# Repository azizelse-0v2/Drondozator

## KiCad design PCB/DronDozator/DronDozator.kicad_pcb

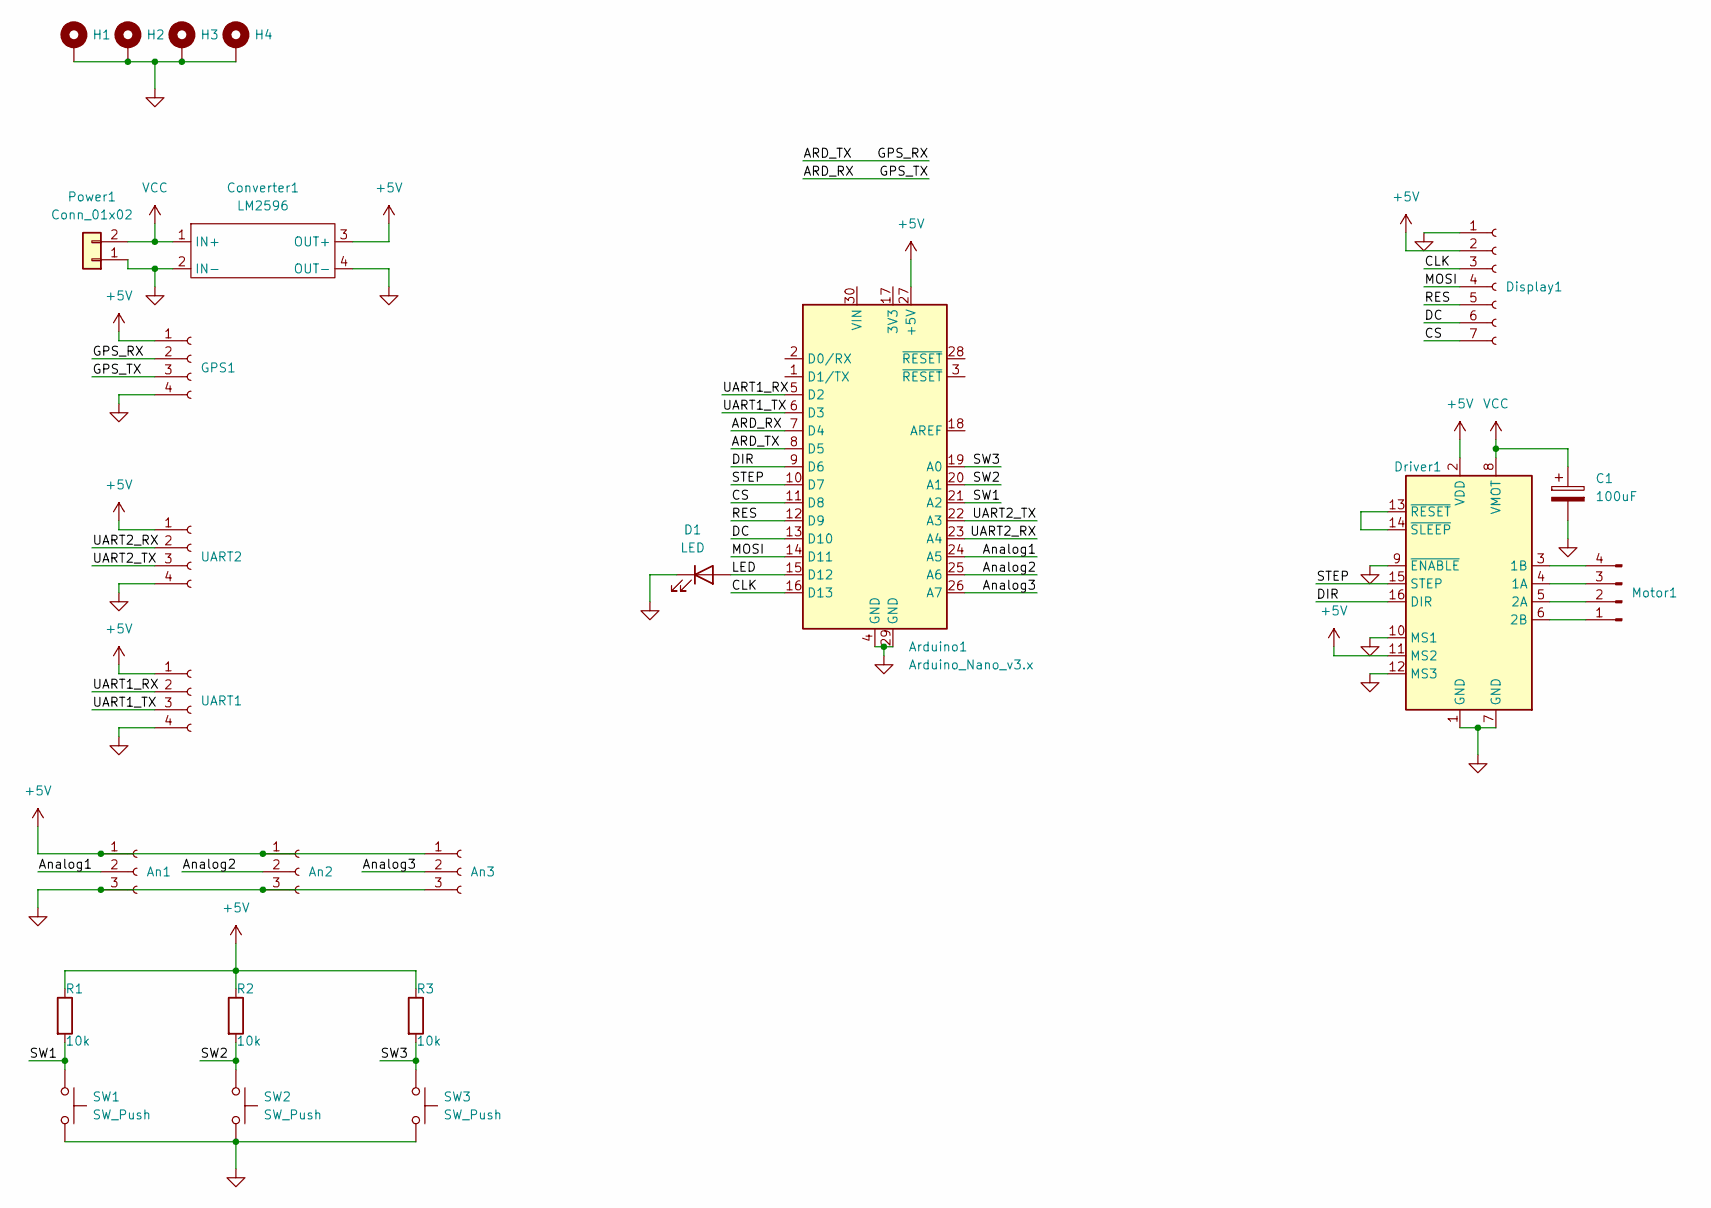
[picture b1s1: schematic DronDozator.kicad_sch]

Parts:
An1, An2, An3: Conn_01x03_Socket; PinSocket_1x03_P2.54mm_Vertical
Arduino1: Arduino_Nano_v3.x; Arduino_Nano
C1: 100uF; CP_Radial_D6.3mm_P2.50mm
Converter1: LM2596
D1: LED; LED_D4.0mm
Display1: Conn_01x07_Socket; PinSocket_1x07_P2.54mm_Vertical
Driver1: Pololu_Breakout_A4988; Pololu_Breakout-16_15.2x20.3mm
GPS1: Conn_01x04_Socket; PinSocket_1x04_P2.54mm_Vertical
H1, H2, H3, H4: MountingHole_Pad; MountingHole_3.5mm_Pad
Motor1: Conn_01x04_Pin; PinHeader_1x04_P2.54mm_Vertical
Power1: Conn_01x02; AMASS_XT60-F_1x02_P7.20mm_Vertical
R1, R2, R3: 10k; R_Axial_DIN0204_L3.6mm_D1.6mm_P7.62mm_Horizontal
SW1, SW2, SW3: SW_Push; SW_PUSH_6mm
UART1, UART2: Conn_01x04_Socket; PinSocket_1x04_P2.54mm_Vertical

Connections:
+5V: An1.1, An2.1, An3.1, Arduino1.27 (+5V), Converter1.3 (OUT+), Display1.2, Driver1.2 (VDD), Driver1.11 (MS2), GPS1.1, R1.1, R2.1, R3.1, UART1.1, UART2.1
/ARD_RX: Arduino1.7 (D4), GPS1.3
/ARD_TX: Arduino1.8 (D5), GPS1.2
/Analog1: An1.2, Arduino1.24 (A5)
/Analog2: An2.2, Arduino1.25 (A6)
/Analog3: An3.2, Arduino1.26 (A7)
/CLK: Arduino1.16 (D13), Display1.3
/CS: Arduino1.11 (D8), Display1.7
/DC: Arduino1.13 (D10), Display1.6
/DIR: Arduino1.9 (D6), Driver1.16 (DIR)
/LED: Arduino1.15 (D12), D1.2 (A)
/MOSI: Arduino1.14 (D11), Display1.4
/RES: Arduino1.12 (D9), Display1.5
/STEP: Arduino1.10 (D7), Driver1.15 (STEP)
/SW1: Arduino1.21 (A2), R1.2, SW1.1
/SW2: Arduino1.20 (A1), R2.2, SW2.1
/SW3: Arduino1.19 (A0), R3.2, SW3.1
/UART1_RX: Arduino1.5 (D2), UART1.2
/UART1_TX: Arduino1.6 (D3), UART1.3
/UART2_RX: Arduino1.23 (A4), UART2.2
/UART2_TX: Arduino1.22 (A3), UART2.3
GND: An1.3, An2.3, An3.3, Arduino1.4 (GND), Arduino1.29 (GND), C1.2, Converter1.2 (IN-), Converter1.4 (OUT-), D1.1 (K), Display1.1, Driver1.1 (GND), Driver1.7 (GND), Driver1.9 (~ENABLE), Driver1.10 (MS1), Driver1.12 (MS3), GPS1.4, H1.1, H2.1, H3.1, H4.1, Power1.1, SW1.2, SW2.2, SW3.2, UART1.4, UART2.4
unnamed: Driver1.4 (1A), Motor1.3
unnamed: Driver1.3 (1B), Motor1.4
unnamed: Driver1.5 (2A), Motor1.2
unnamed: Driver1.6 (2B), Motor1.1
unnamed: Driver1.13 (~RESET), Driver1.14 (~SLEEP)
VCC: C1.1, Converter1.1 (IN+), Driver1.8 (VMOT), Power1.2

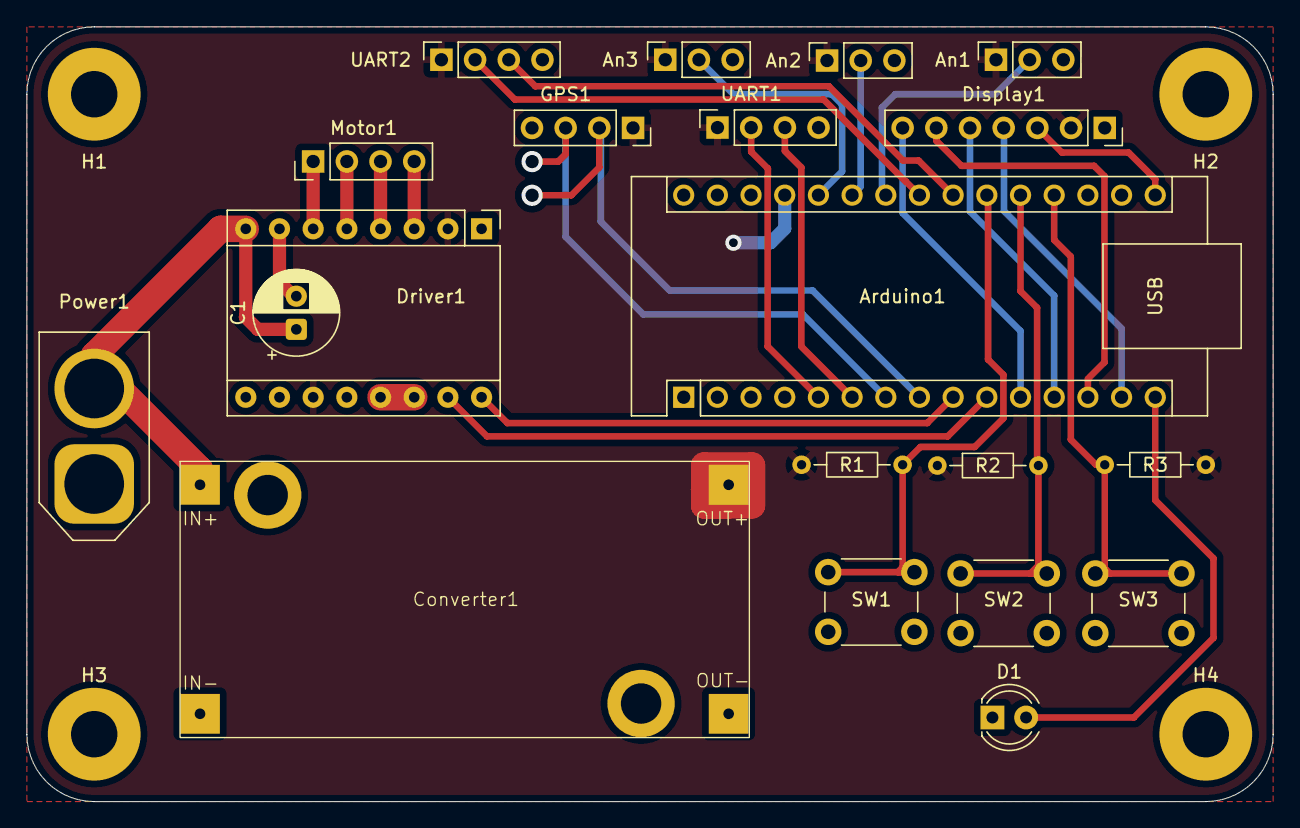
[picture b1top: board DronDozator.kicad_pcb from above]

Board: 2 copper layers, 94.0 x 58.4 mm, 24 parts (0 on the bottom side), 28 nets.

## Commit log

2026-03-13 Number of satellites on SPI screen
2026-03-13 Added stepper test
2026-03-13 Added schem
2026-03-13 Moved stls to a seperate folder
2026-03-14 Finalized schem
2026-03-14 Started FC schem
2026-03-14 Modified schem
2026-03-15 Removed Duplicate
2026-03-16 Add Apache License 2.0 to the project
2026-03-16 Moved from CubeIDE to vscode
